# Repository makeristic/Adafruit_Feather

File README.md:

# Adafruit Feather KiCad template

A KiCad project template for designing boards around the [Adafruit Feather specification](https://learn.adafruit.com/adafruit-feather/feather-specification). It provides the board outline, mounting holes, 12-pin and 16-pin headers, a Micro-USB connector, and a two-pin JST PH battery connector.

## Status

This is a starting layout, with no routed PCB tracks. Add your own controller, power circuitry, and application circuit before fabrication. The checked-in PCB was saved by KiCad 5.1.2; its legacy schematic and project formats are retained. The [correctness audit](docs/code-audit-report.md) confirms schematic/PCB connector-net agreement and records remaining ERC, DRC, and mounting-hole concerns. It does not establish electrical or manufacturing validation.

## Use the template

```sh
git clone https://github.com/makeristic/Adafruit_Feather.git
```

1. Copy the `Adafruit_Feather` directory, including `meta/`, into your KiCad user templates directory. The archived [KiCad 5.1 template-location documentation](https://docs.kicad.org/5.1/en/kicad/kicad.html#template_locations) describes the directory layout.
2. In KiCad, create a project from a template and select this template under User Templates. Alternatively, open [Adafruit_Feather.pro](Adafruit_Feather.pro) to inspect the source.
3. Install KiCad's standard symbol, footprint, and 3D-model libraries. The source uses standard `Connector`, `Connector_Generic`, and `power` symbols and connector footprints. Retain the supplied `-cache.lib` when opening the legacy schematic. Models reference `${KISYS3DMOD}`; when using a newer release, check that this legacy path variable points to your installed 3D-model directory and resolve any changed model filenames.
4. Work in a copy when opening with a newer KiCad release, which may convert the legacy files. Review the Feather pinout, connector orientation, and power circuitry, then run ERC and DRC on your completed design.

## Files

- [Adafruit_Feather.sch](Adafruit_Feather.sch): legacy schematic with connector pin labels.
- [Adafruit_Feather.kicad_pcb](Adafruit_Feather.kicad_pcb): board outline and placed footprints.
- [Adafruit_Feather-cache.lib](Adafruit_Feather-cache.lib): cached schematic symbols.
- [meta/](meta/): KiCad template description, icon, and board preview.

No firmware, BOM export, or Gerber fabrication package is included.

## Related projects and contributions

Use [Adafruit_Feather_USB-C](https://github.com/makeristic/Adafruit_Feather_USB-C) for the USB-C variant. [Feather_STM32WB55](https://github.com/makeristic/Feather_STM32WB55) is a separate STM32WB55 board design; [Makeristic-KiCad-Library](https://github.com/makeristic/Makeristic-KiCad-Library) contains additional parts.

Report problems through [GitHub issues](https://github.com/makeristic/Adafruit_Feather/issues), including your KiCad version and any missing-library messages. For layout changes, include schematic or board screenshots and explain any change to Feather compatibility.

## Attribution and licence

Original template copyright © 2019 [arturo182](https://twitter.com/arturo182), from [KiCad/kicad-templates pull request #23](https://github.com/KiCad/kicad-templates/pull/23/files#diff-a7a7ac8a622f8aa19b54fb2f3cf42329). This Makeristic repository preserves that template and its attribution.

The [upstream licence at the source revision](https://github.com/KiCad/kicad-templates/blob/459d6bc93c55cfdac9f9b5d629b44cb891b5f2b8/LICENSE.md) is Creative Commons Attribution-ShareAlike 4.0 with the KiCad library exception. A copy is included in [LICENSE.md](LICENSE.md). The existing template has not been relicensed to MIT; consult the licence for the distinction between using library data in a design and redistributing the template collection.

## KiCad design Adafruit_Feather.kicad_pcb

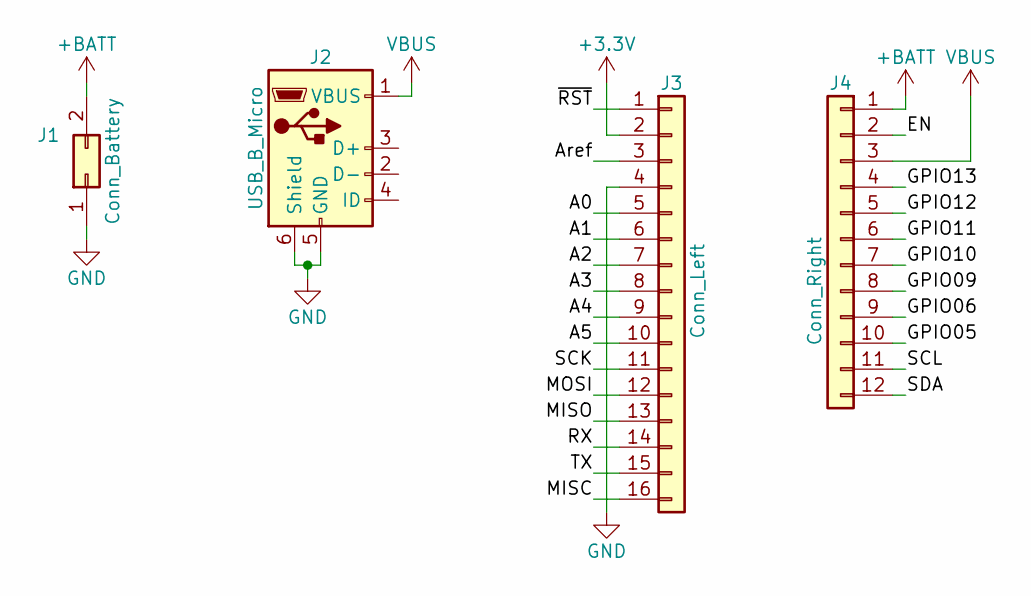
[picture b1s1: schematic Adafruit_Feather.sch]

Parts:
J1: Conn_Battery; JST_PH_B2B-PH-SM4-TB_1x02-1MP_P2.00mm_Vertical
J2: USB_B_Micro; USB_Micro-B_Molex-105017-0001
J3: Conn_Left; PinSocket_1x16_P2.54mm_Vertical
J4: Conn_Right; PinSocket_1x12_P2.54mm_Vertical

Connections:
+3V3: J3.2
+BATT: J1.2, J4.1
/A0: J3.5
/A1: J3.6
/A2: J3.7
/A3: J3.8
/A4: J3.9
/A5: J3.10
/Aref: J3.3
/EN: J4.2
/GPIO05: J4.10
/GPIO06: J4.9
/GPIO09: J4.8
/GPIO10: J4.7
/GPIO11: J4.6
/GPIO12: J4.5
/GPIO13: J4.4
/MISC: J3.16
/MISO: J3.13
/MOSI: J3.12
/RX: J3.14
/SCK: J3.11
/SCL: J4.11
/SDA: J4.12
/TX: J3.15
/~RST~: J3.1
GND: J1.1, J2.5 (GND), J2.6 (Shield), J3.4
VBUS: J2.1 (VBUS), J4.3

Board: 2 copper layers, 4 parts (0 on the bottom side), 3 nets, no tracks yet.
